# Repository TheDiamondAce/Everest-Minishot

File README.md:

# Everest-Minishot

# Motivation
I wanted to make a camera that was accesible and very good quality, everywhere you go without making it too much of a hassle to take a picture in, whether it be in nature, in rain, in the bustling cities, or in a secluded area. Anywhere, anytime, without any friction to composition.

# What it is
This project is a camera that will be able to be hung on your keychain, being able to take videos and picture without friction, from turning it on to getting the composition like how you see it. It will be similar to that of the dji nano. And will be GREAT! alr probably gonna change that later lmao

# How to build

To build, you will need to get the chassis by 3D printing it, order the PCB as in the Repo, buy a raspberry pi zero 2 W, and also get the battery as shown in the B.O.M, then to build, you will need to screw in the components in the enclourse. Then after, you will need to follow the wiring diagram as shown in the PCB files, connected the buttons as shown in the PCB wiring respectively. For the Display you will need to connect the SDA to GPIO 27 and SDL to GPIO 22, since the sda and scl native ports on the raspeberry pi is being occupied by the buttons, after that, you would need to connect the battery to the bms you will then need to drag everything in the code file and put it to the root of the raspberry pi zero 2w so that it runs on startup. Then after you will have to get the code from the code file and flash it to the raspberry pi zero 2w. Then after its just a matter of turning the camera on and taking pictures seamelessly!

# BOM
| Name                                                                                          | Description                                                                           | Total (USD) | Quantity                                | Why                                                                                              | Link                                                                                                                                                                                                                                                                                                                                                                                                                                                                                                                                                                                                                                    |
|-----------------------------------------------------------------------------------------------|---------------------------------------------------------------------------------------|-------------|-----------------------------------------|--------------------------------------------------------------------------------------------------|-----------------------------------------------------------------------------------------------------------------------------------------------------------------------------------------------------------------------------------------------------------------------------------------------------------------------------------------------------------------------------------------------------------------------------------------------------------------------------------------------------------------------------------------------------------------------------------------------------------------------------------------|
| 12mm Button                                                                                   | A tactile switch that either connects a cirucuit or disconnects depending on input    | $8.12       | 2                                       | So you can click stuff to memorize for the minigame                                              | https://www.amazon.com/Uxcell-a11111400ux0132-Momentary-Tactile-Button/dp/B0090VQLDK                                                                                                                                                                                                                                                                                                                                                                                                                                                                                                                                                    |
| SH 1107 OLED                                                                                  | Display used to show camera input and modes                                           | $12.39      | 1                                       | To see what inputs to do next and other data                                                     | https://www.amazon.com/ACEIRMC-ILI9341-Display-Touch-240X320/dp/B0C4D5S6G5/ref=sr_1_10_sspa?crid=1KKGFFL8GGC72&dib=eyJ2IjoiMSJ9.aNbS-hCnwROiq-lihDWLj0bSTkExzZcUEg9Thz-MRRtS2XSDTZusdgq0aD1F0WmFP2z1icua7XtMO6m0dMOpn8SqrOFp1HIlcN4kiqw6-RlV7hZO4ruwCns7e_xrwwarWxaiSyrChwiIRUrUY_RlX9OKgmKKALx-gO4lSBbiMaZfKv6a7KsmvzFghX94ueB0tjP9qSX40MXT01v37X8MMYSJqIt6UnkreQ59ftwFdiegDUDVujNbTPq7P3rk02P9OOVeiCEMzoFH8qXlYbO1NNMZsi5VeRhwTNT7sHwGj98.L9Ilfuyvs66CsTIbDNYf3OsazpswS6k4iaS05y2B6dk&dib_tag=se&keywords=ili9341&qid=1781262418&s=electronics&sprefix=ili%2Celectronics%2C409&sr=1-10-spons&sp_csd=d2lkZ2V0TmFtZT1zcF9tdGY&psc=1     |
| Arduino Zero 2 W                                                                              | The Microcontroller that will control all functions of the minigame as well as logic. | $15.00      | 1                                       | To control the whole camera and logic                                                            | https://www.raspberrypi.com/products/raspberry-pi-zero-2-w/                                                                                                                                                                                                                                                                                                                                                                                                                                                                                                                                                                             |
| Dupont Female-Female Wires                                                                    | Used to connect modules to microcontroller and circuits.                              | $6.98       | 5                                       | Bruh, so the whole thing can get some electricity.                                               | https://www.amazon.com/California-JOS-Breadboard-Optional-Multicolored/dp/B0BRTKTV64?th=1                                                                                                                                                                                                                                                                                                                                                                                                                                                                                                                                               |
| 3D Printer Enclousure.                                                                        | The host for all modules necessary in the build                                       | 1           | To put all of the modules into one area | can print through hackclub or by yourself with step file                                         |                                                                                                                                                                                                                                                                                                                                                                                                                                                                                                                                                                                                                                         |
| Sony IMX576 24MP Camera                                                                       | A module that uses photons to create an image (a camera)                              | $18.30      | 1 rough price*                          | So the camera becomes a camera                                                                   | https://sincerefirst.en.made-in-china.com/product/BANRFcJrLdWv/China-24MP-Sony-Imx576-Image-Sensor-Autofocus-Lens-24-Pin-Camera-Module-Smartphone.html                                                                                                                                                                                                                                                                                                                                                                                                                                                                                  |
| Ribbon Flex Extension Cables for Pi Zero&W                                                    | A 15mm to 22mm ribbion cable                                                          | $8.99       | 1                                       | So the IMX576 can connect to the Rasberry Pi Zero 2W                                             | https://www.amazon.com/Arducam-Raspberry-Camera-Ribbon-Extension/dp/B085RW9K13/?_encoding=UTF8&pd_rd_w=x8UbO&content-id=amzn1.sym.a9c4acee-9ca0-46be-bae3-532a2b4b0d29%3Aamzn1.symc.5a16118f-86f0-44cd-8e3e-6c5f82df43d0&pf_rd_p=a9c4acee-9ca0-46be-bae3-532a2b4b0d29&pf_rd_r=9X4HZN75VZ4YB08QZNPW&pd_rd_wg=kdRp2&pd_rd_r=617b9bf0-440a-42f2-9107-20efd28b610a&ref_=pd_hp_d_atf_ci_mcx_mr_                                                                                                                                                                                                                                              |
| USB C connector                                                                               | A module in which a usb C port is included                                            | $7.49       | 1                                       | For easy connectivity for the camera for data and power.                                         | https://www.amazon.com/Teansic-Connector-Breakout-Converter-Transfer/dp/B0B4J5NJ2Y/ref=sr_1_3?crid=3IMY4LTK8CFVK&dib=eyJ2IjoiMSJ9._TAav2gmYgzR2fvtTjBYdAncdrRe2JEXz48orUvk4PvnixvgSd7BiMozddiG7ZqMbsxeniI0Ob2XsravI7RVDWU9wPSSekozCTOZsiTwrHoj6EjdCvLMxAoIVEarxsqKP2s8pnMNgndUzJS0R_ih4MMafPWaCmU0tkK2XNSFuRgQQ34bmeG-38jUrw3OvX0DvpUaffIyZVBVBOiWMfQ7aq90x1VNnlj6ZZpW5zrZNUPzYi4rJBfmeRi_U5-NS81sxeag735exzMIqGvhppiLU2VINXloYt8rCbBx6tvqG2A.UchCu6BU6WBTt3usZwzm49mGplQKhnHKdiVavSk4A58&dib_tag=se&keywords=usb%2Bc%2Bconnector%2Bmodule&qid=1781853104&s=industrial&sprefix=usb%2Bc%2Bconnector%2Bmod%2Cindustrial%2C388&sr=1-3&th=1 |
| JST Male Header                                                                               | A module that allows for female JST wires to connect                                  | $0.04       | 2                                       | For Carrier PCB connection to Raspberry PI 2W                                                    | https://www.taydaelectronics.com/3-pins-jst-xh-2-54-male-connector-straight-180-degree.html                                                                                                                                                                                                                                                                                                                                                                                                                                                                                                                                             |
| Female to Female JST XH 3pin                                                                  | A module in which connects to the male headers pins                                   | $1.80       | 1                                       | ~~~~                                                                                             | https://www.pololu.com/product/5513                                                                                                                                                                                                                                                                                                                                                                                                                                                                                                                                                                                                     |
| A Lithium Li-ion 18650 3.7V Battery Charger Module DC 5V Converter Power Supply               | A module that steps up 3.7 to constant 5v through battery                             | $2.40       | 1                                       | To actually make the battery work with raspberry pi 2w charging and ewnabling it to run portable | https://www.ebay.co.uk/itm/266207466564                                                                                                                                                                                                                                                                                                                                                                                                                                                                                                                                                                                                 |
| JST XH Female to Dupont 4Pin                                                                  | A cable that has a 4 pin JST XH connector that splits into dupont cables              | $0.40       | 1                                       | To connect the oled display to the raspeberry pi                                                 | https://grobotronics.com/jumper-wire-jst-xh-to-separate-dupont.html?variation_id=17936                                                                                                                                                                                                                                                                                                                                                                                                                                                                                                                                                  |
| PCB                                                                                           | A electrical component custom made for a specific task                                | $30.71      | 1                                       | For the buttons up top to connect to the rasberry PI Zero.                                       | https://www.pcbway.com/orderonline.aspx?outsideid=b538974d-ef2e-4f84-a5e9-d126d94cb61b                                                                                                                                                                                                                                                                                                                                                                                                                                                                                                                                                  |
| THE LINKS USED MIGHT HAVE MULTIPLE PIECES SINCE THEY ARE THE BEST BANG FOR BUCK ON AMAZON.*** |                                                                                       |             |                                         |                                                                                                  |                                                                                                                                                                                                                                                                                                                                                                                                                                                                                                                                                                                                                                         |
|                                                                                               | MIGHT BE ABLE TO ASK FOR A SAMPLE PIECE, OTHERWISE ITS 185.82**                       |             |                                         |                                                                                                  |                                                                                                                                                                                                                                                                                                                                                                                                                                                                                                                                                                                                                                         |
|                                                                                               |                                                                                       |             |                                         |                                                                                                  |                                                                                                                                                                                                                                                                                                                                                                                                                                                                                                                                                                                                                                         |
|                                                                                               | TOTAL =                                                                               | $112.62     |                                         |                                                                                                  |                                                                                                                                                                                                                                                                                                                                                                                                                                                                                                                                                                                                                                         |

# CAD

## Isometric

## Front

## Side

## Back

# Wiring Diagram/PCB

(The 01x03 jst connecter will be connected to the GPIO 3 and GPIO 4 pins as well as GND pin respectively)

# Photo Taken of Live Viewfinder for the Camera (Everest Minishot Simulator)

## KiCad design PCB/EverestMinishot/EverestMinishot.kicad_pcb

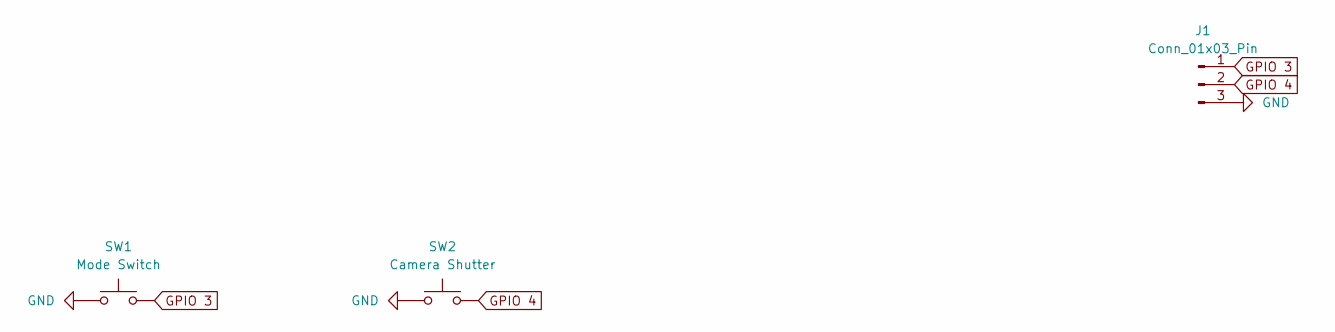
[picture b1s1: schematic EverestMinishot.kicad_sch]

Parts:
J1: Conn_01x03_Pin; PinHeader_1x03_P2.54mm_Vertical
SW1: Mode Switch; SW_PUSH-12mm
SW2: Camera Shutter; SW_PUSH-12mm

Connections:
GND: J1.3, SW1.1, SW2.1
GPIO 3: J1.1, SW1.2
GPIO 4: J1.2, SW2.2

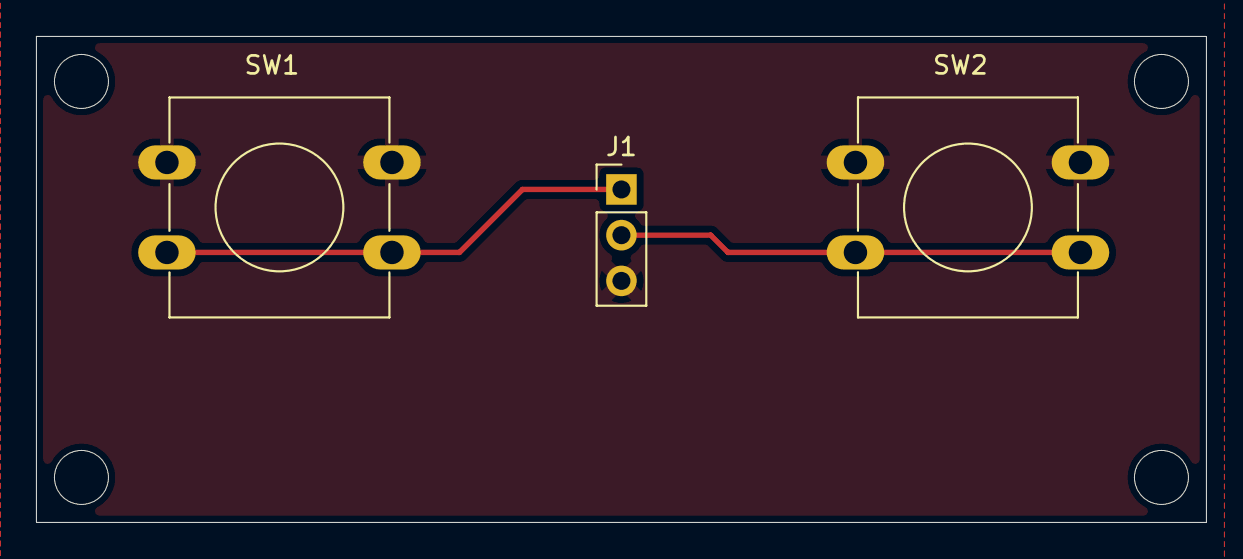
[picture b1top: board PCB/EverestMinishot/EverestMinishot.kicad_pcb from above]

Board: 2 copper layers, 65.0 x 27.0 mm, 3 parts (0 on the bottom side), 3 nets.

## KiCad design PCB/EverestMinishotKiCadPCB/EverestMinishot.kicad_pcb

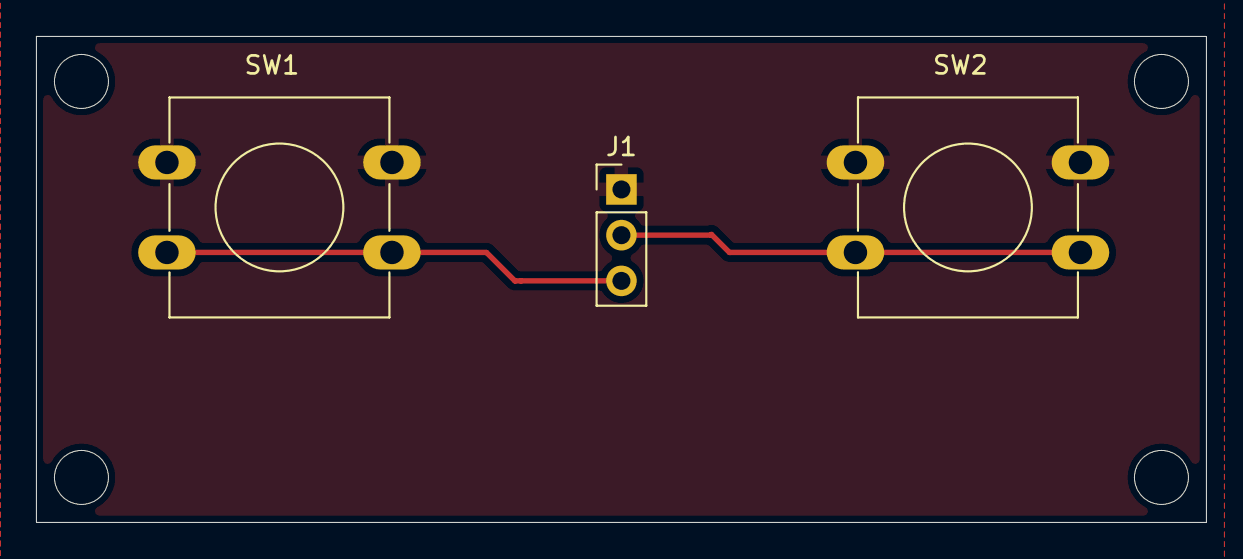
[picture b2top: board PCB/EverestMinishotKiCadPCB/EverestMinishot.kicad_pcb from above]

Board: 2 copper layers, 65.0 x 27.0 mm, 3 parts (0 on the bottom side), 3 nets.

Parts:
J1: Conn_01x03_Pin; PinHeader_1x03_P2.54mm_Vertical
SW1: Mode Switch; SW_PUSH-12mm
SW2: Camera Shutter; SW_PUSH-12mm

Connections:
GND: J1.1, SW1.1, SW2.1
GPIO 17: J1.2, SW2.2
GPIO 27: J1.3, SW1.2

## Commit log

2026-06-20 made the gitingore and added pcbway gerber
    IN this update, I added the gerber files
2026-06-20 Rename gitignore.txt to .gitignore
2026-06-20 added plot files, cad and pcb
2026-06-20 Made Code for Camera to work
    In this update I made it so the camera would work using python code.
2026-06-20 Expand README with project details and images
    Added detailed sections on motivation, project description, building instructions, CAD images, and wiring diagram.
2026-06-20 Updated CSV
2026-06-20 Put PCB into folder and added .f3z
2026-06-20 Add photo section to README
2026-06-20 Update section title for camera photo
2026-06-21 organized gerber files
2026-06-21 Added Others to Different File
2026-06-21 Update section title for camera photo description
2026-06-21 Made zine bit better
2026-06-21 fixed up duplicates
2026-06-21 Replace image in README with updated version
    Updated image in README.md to a new source with different dimensions.
2026-06-21 Added Age Name Country on Zine
    In this update, I updated the zine to match
2026-06-23 updated zine and cad
2026-06-23 Update .gitignore to remove BOM file exclusions
    Remove exported BOM file patterns from .gitignore
2026-06-27 fixing issues pt1
